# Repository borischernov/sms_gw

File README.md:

# sms_gw

4-channel SMS gateway based on SIM808 modules

Module example: https://www.amazon.com/MagiDeal-SIM800L-Transfer-Module-Arduino/dp/B01FRUJ6TI/ref=sr_1_10?ie=UTF8&qid=1493729026&sr=8-10&keywords=sim800l

ATTINY2313 MCU is optional and intended for resetting GSM modules on demand.

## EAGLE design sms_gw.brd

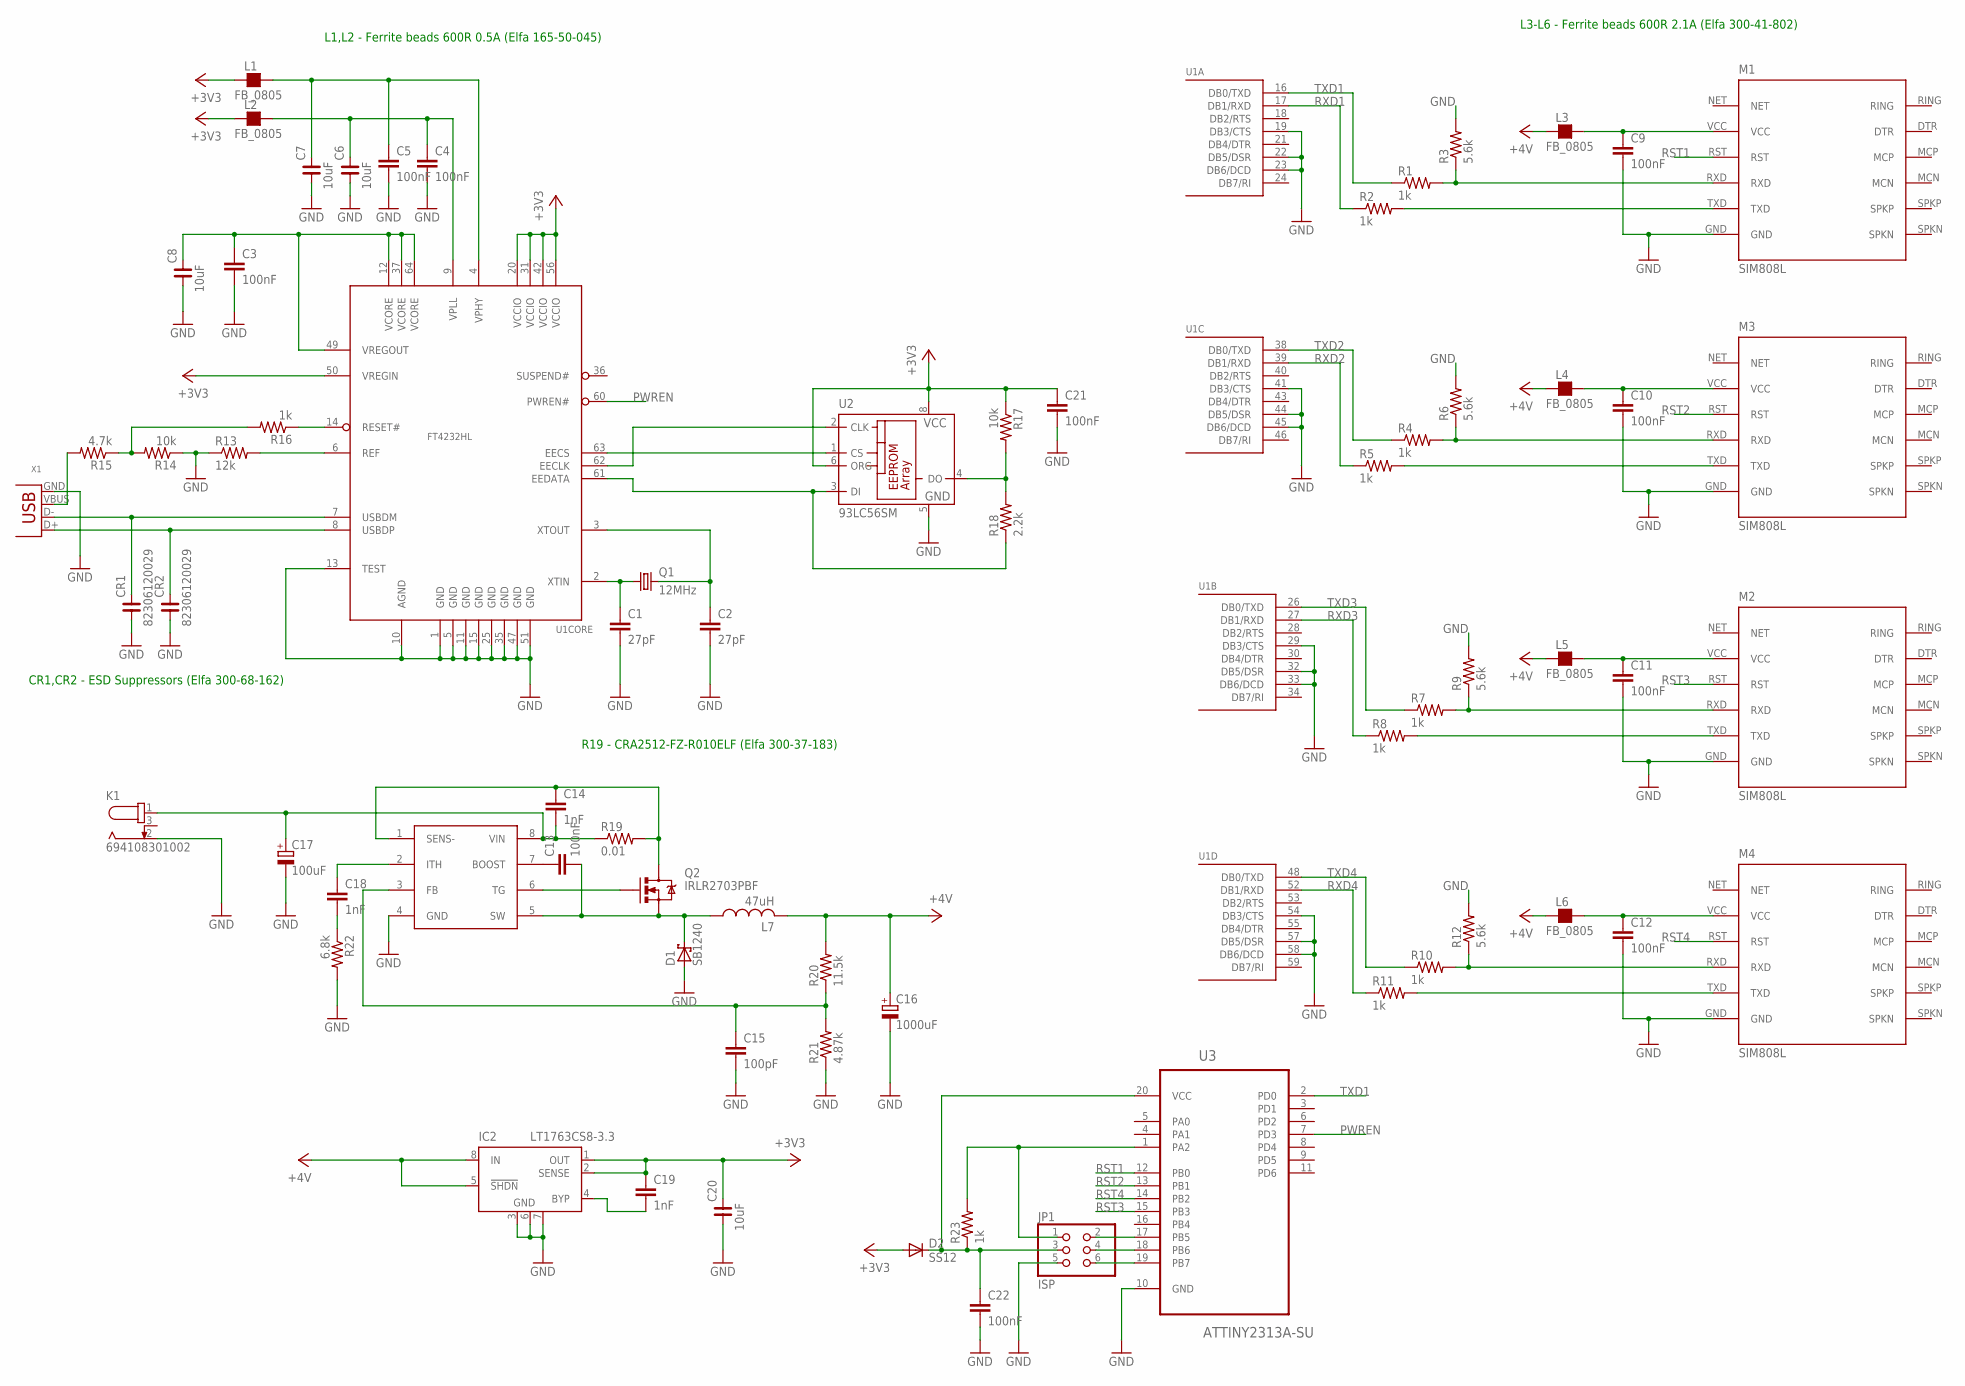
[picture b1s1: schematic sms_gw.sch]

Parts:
C1, C2: 27pF; C0805
C3, C4, C5, C9, C10, C11, C12, C21, C22: 100nF; C0805
C6, C7, C8, C20: 10uF; C1210
C13: 100nF; C1206
C14, C18, C19: 1nF; C0805
C15: 100pF; C0805
C16: 1000uF; E5-8,5
C17: 100uF; E5-8,5
CR1, CR2: 82306120029; C0603
D1: SB1240; F126Z12
D2: SS12; DO-214AC
IC1: LTC1624S8; SO08
IC2: LT1763CS8-3.3; SOIC8
JP1: ISP; 2X03
K1: 694108301002
L1, L2, L3, L4, L5, L6: FB_0805; L0805
L7: 47uH; TJ3-U2
M1, M2, M3, M4: SIM808L; SIM800L
Q1: 12MHz; HC49U-V
Q2: IRLR2703PBF; DPAK
R1, R2, R4, R5, R7, R8, R10, R11, R16, R23: 1k; R0805
R3, R6, R9, R12: 5.6k; R0805
R13: 12k; R0805
R14, R17: 10k; R0805
R15: 4.7k; R0805
R18: 2.2k; R0805
R19: 0.01; R2512
R20: 11.5k; R0603
R21: 4.87k; R0603
R22: 6.8k; R0805
U1: FT4232HL; LQFP64
U2: 93LC56SM; SO-08M
U3: ATTINY2313A-SU; SOIC127P1032X265-20N
X1: USB-B-H

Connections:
+1V8: C3.1, C8.2, U1.12 (VCORE), U1.37 (VCORE), U1.49 (VREGOUT), U1.64 (VCORE)
+3V3: C19.1, C20.2, C21.1, D2.A, IC2.1 (OUT), IC2.2 (SENSE), L1.1, L2.1, R17.1, U1.20 (VCCIO), U1.31 (VCCIO), U1.42 (VCCIO), U1.50 (VREGIN), U1.56 (VCCIO), U2.6 (ORG), U2.8 (VCC)
+4V: C16.+, IC2.5 (!SHDN), IC2.8 (IN), L3.1, L4.1, L5.1, L6.1, L7.2, R20.2
GND: C1.2, C2.2, C3.2, C4.2, C5.2, C6.1, C7.1, C8.1, C9.2, C10.2, C11.2, C12.2, C15.2, C16.-, C17.-, C20.1, C21.2, C22.2, CR1.1, CR2.1, D1.A, IC1.4 (GND), IC2.3 (GND), IC2.6 (GND), IC2.7 (GND), JP1.5, K1.2, M1.GND, M2.GND, M3.GND, M4.GND, R3.2, R6.2, R9.2, R12.2, R13.1, R14.1, R21.1, R22.2, U1.1 (GND), U1.5 (GND), U1.10 (AGND), U1.11 (GND), U1.13 (TEST), U1.15 (GND), U1.19 (DB3/CTS), U1.22 (DB5/DSR), U1.23 (DB6/DCD), U1.25 (GND), U1.29 (DB3/CTS), U1.32 (DB5/DSR), U1.33 (DB6/DCD), U1.35 (GND), U1.41 (DB3/CTS), U1.44 (DB5/DSR), U1.45 (DB6/DCD), U1.47 (GND), U1.51 (GND), U1.54 (DB3/CTS), U1.57 (DB5/DSR), U1.58 (DB6/DCD), U2.5 (GND), U3.10 (GND), X1.GND
unnamed: M3.TXD, R5.2
unnamed: M1.TXD, R2.2
unnamed: M1.RXD, R1.2, R3.1
unnamed: JP1.2, U3.17 (PB5)
unnamed: M3.RXD, R4.2, R6.1
unnamed: M2.TXD, R8.2
unnamed: M2.RXD, R7.2, R9.1
unnamed: M4.TXD, R11.2
unnamed: C22.1, D2.C, JP1.3, R23.1, U3.20 (VCC)
unnamed: M4.RXD, R10.2, R12.1
unnamed: C9.1, L3.2, M1.VCC
unnamed: C1.1, Q1.1, U1.2 (XTIN)
unnamed: C2.1, Q1.2, U1.3 (XTOUT)
unnamed: R13.2, U1.6 (REF)
unnamed: CR1.2, U1.7 (USBDM), X1.D-
unnamed: CR2.2, U1.8 (USBDP), X1.D+
unnamed: C5.1, C7.2, L1.2, U1.4 (VPHY)
unnamed: C4.1, C6.2, L2.2, U1.9 (VPLL)
unnamed: R16.1, U1.14 (RESET#)
unnamed: R15.2, X1.VBUS
unnamed: R14.2, R15.1, R16.2
unnamed: C10.1, L4.2, M3.VCC
unnamed: C11.1, L5.2, M2.VCC
unnamed: C12.1, L6.2, M4.VCC
unnamed: U1.63 (EECS), U2.1 (CS)
unnamed: U1.62 (EECLK), U2.2 (CLK)
unnamed: IC1.6 (TG), Q2.1 (G)
unnamed: R17.2, R18.2, U2.4 (DO)
unnamed: R18.1, U1.61 (EEDATA), U2.3 (DI)
unnamed: C13.2, D1.C, IC1.5 (SW), L7.1, Q2.3 (S)
unnamed: C13.1, IC1.7 (BOOST)
unnamed: C14.2, C17.+, IC1.8 (VIN), K1.1, R19.1
unnamed: C14.1, IC1.1 (SENS-), Q2.4 (D), R19.2
unnamed: C15.1, IC1.3 (FB), R20.1, R21.2
unnamed: C18.1, IC1.2 (ITH)
unnamed: C18.2, R22.1
unnamed: C19.2, IC2.4 (BYP)
unnamed: JP1.4, U3.18 (PB6)
unnamed: JP1.6, U3.19 (PB7)
unnamed: JP1.1, R23.2, U3.1 (PA2)
PWREN: U1.60 (PWREN#), U3.7 (PD3)
RST1: M1.RST, U3.12 (PB0)
RST2: M3.RST, U3.13 (PB1)
RST3: M2.RST, U3.15 (PB3)
RST4: M4.RST, U3.14 (PB2)
RXD1: R2.1, U1.17 (DB1/RXD)
RXD2: R5.1, U1.39 (DB1/RXD)
RXD3: R8.1, U1.27 (DB1/RXD)
RXD4: R11.1, U1.52 (DB1/RXD)
TXD1: R1.1, U1.16 (DB0/TXD), U3.2 (PD0)
TXD2: R4.1, U1.38 (DB0/TXD)
TXD3: R7.1, U1.26 (DB0/TXD)
TXD4: R10.1, U1.48 (DB0/TXD)

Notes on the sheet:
L1,L2 - Ferrite beads 600R 0.5A (Elfa 165-50-045)
L3-L6 - Ferrite beads 600R 2.1A (Elfa 300-41-802)
R19 - CRA2512-FZ-R010ELF (Elfa 300-37-183)
CR1,CR2 - ESD Suppressors (Elfa 300-68-162)

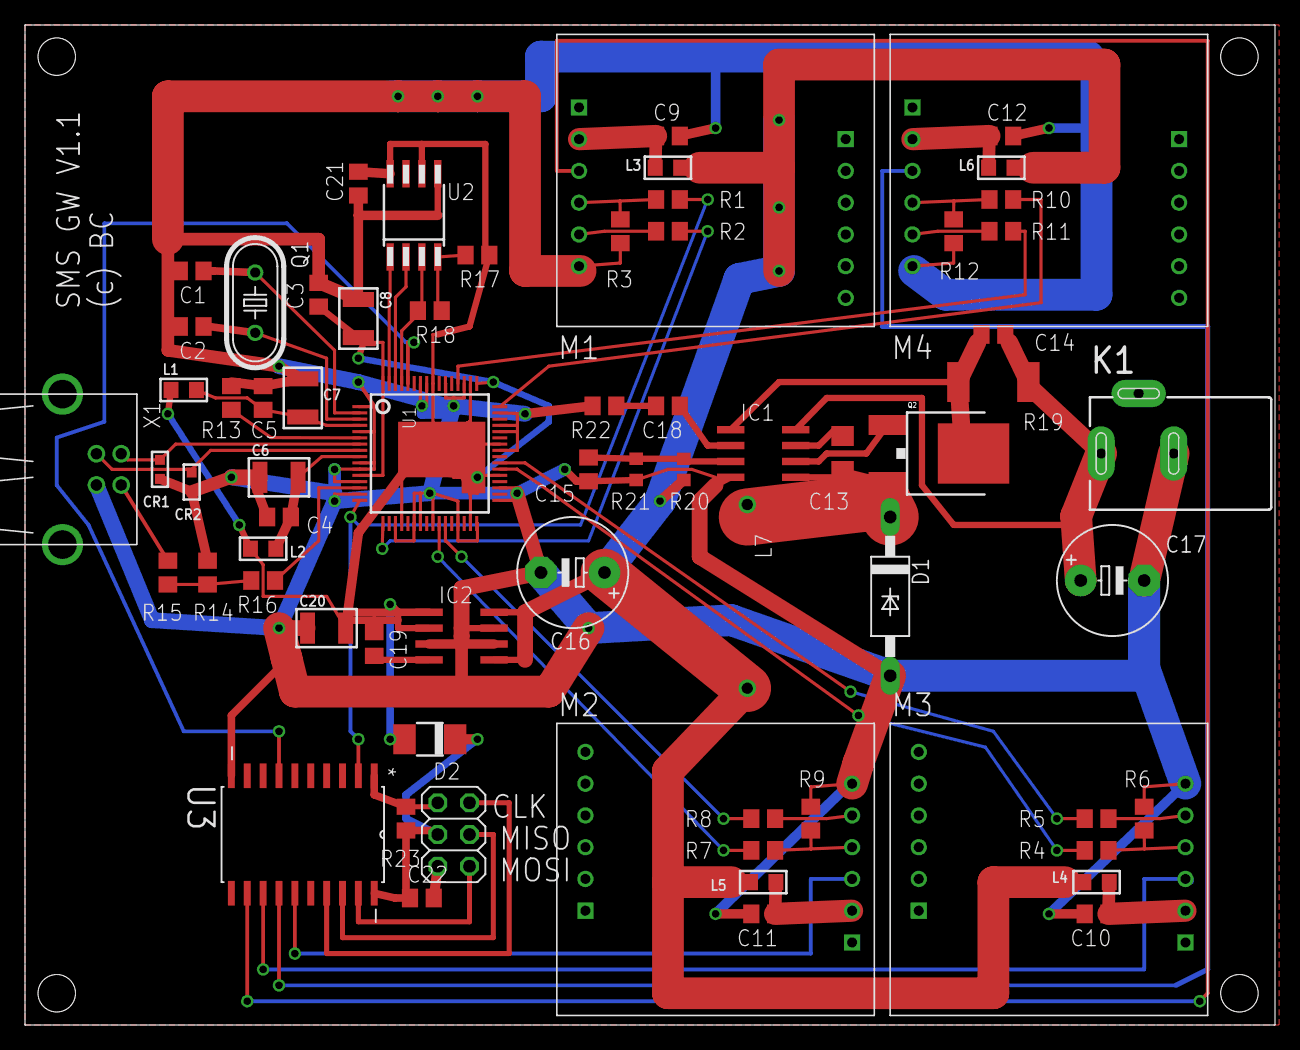
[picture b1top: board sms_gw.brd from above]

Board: 2 copper layers, 100.0 x 80.0 mm, 70 parts (0 on the bottom side), 57 nets.

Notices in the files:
parts and their libraries:
rc-master-smd: Copyright (C) 2007, Bob Starr
Wurth_Elektronik_Electromechanic_DC_Powe: Copyright: Würth Elektronik
SparkFun-DiscreteSemi: Licensing: Creative Commons ShareAlike 4.0 International - https://creativecommons.org/licenses/by-sa/4.0
